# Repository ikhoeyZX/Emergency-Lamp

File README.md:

# Undens Lampu Emergency

This repository contains the source code for build a Emergency lamp based STM8 or ESP8266.

* Note: ESP8266 version are __not recommended__ but you can build it, but beware it sometimes crash and heating up when using step-up ic / module at low battery level (below 3V)

# Reason?

In my country there is much earthquake, well because i'm life in ring of fire area, i did experience big earthquake back in 2017. When earthquake happen, my family still sleeping (it around 12AM) and got blackout, there is no way to find door or find a place to protect our selfes because it's too dark to see. So that's why i make this in case it happen again we still got light to find exit or place to protect out selfes.

Most commercial emergency lamp in here are bad because cheap battery (only last 1 year and only hold 1.5h every running) and didn't have protection charger!!

# What version i should make?

There is 2 build exist (ESP8266 and STM8, arduino series will added later) for 1 layer recommended use v1.2 and for 2 layers smd build use v1.3

each folder contains how to build it. You need Android IDE to program it (in STM8 case, make sure your username in PC doesn't have "space" otherwise SDCPP will fail to build because this bug not yet fixed from SDCC it self).

* Note : For step-up ic/module you can find by self, depend of budget, because MOSFET output only act as "switch" so you need step-up to make sure it can output high voltage to light a leds (5v are common but waste much power, i recommended use 4.3v output to reduce power usage)
* MOSFET should be withstand around ~4A continues with heatsink, so if you using step-up and output set 4.3v it should be around ~4A Max in input side
* In my case only use 1A at MOSFET output and 4400mA battery. it can run without issue around 4H with 20 leds (~30mA/leds) in 12 places at home.

## Finished device:

|                      **Main device**                          |                                      **A Step up ic MT3608**                                   |
| :-----------------------------------------------------------: | :--------------------------------------------------------------------------------------------: |
|                       |                                                         |

|               **Main device when running**                    |                  **A led that used, smd led 3v with 5v input (with 47ohm resistor)**           |
| :-----------------------------------------------------------: | :--------------------------------------------------------------------------------------------: |
|          |  |

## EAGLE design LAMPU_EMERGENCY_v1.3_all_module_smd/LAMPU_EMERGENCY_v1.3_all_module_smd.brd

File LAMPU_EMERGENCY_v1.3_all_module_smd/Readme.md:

To make this follow "Build.png"

for output you need external step-up, you can use MT3608 / QC 3.0 or other step-up, 5v output is recommended for better battery life

for 2A or higher put heatsink in MOSFET!

for speaker, this build use "buzzer type"

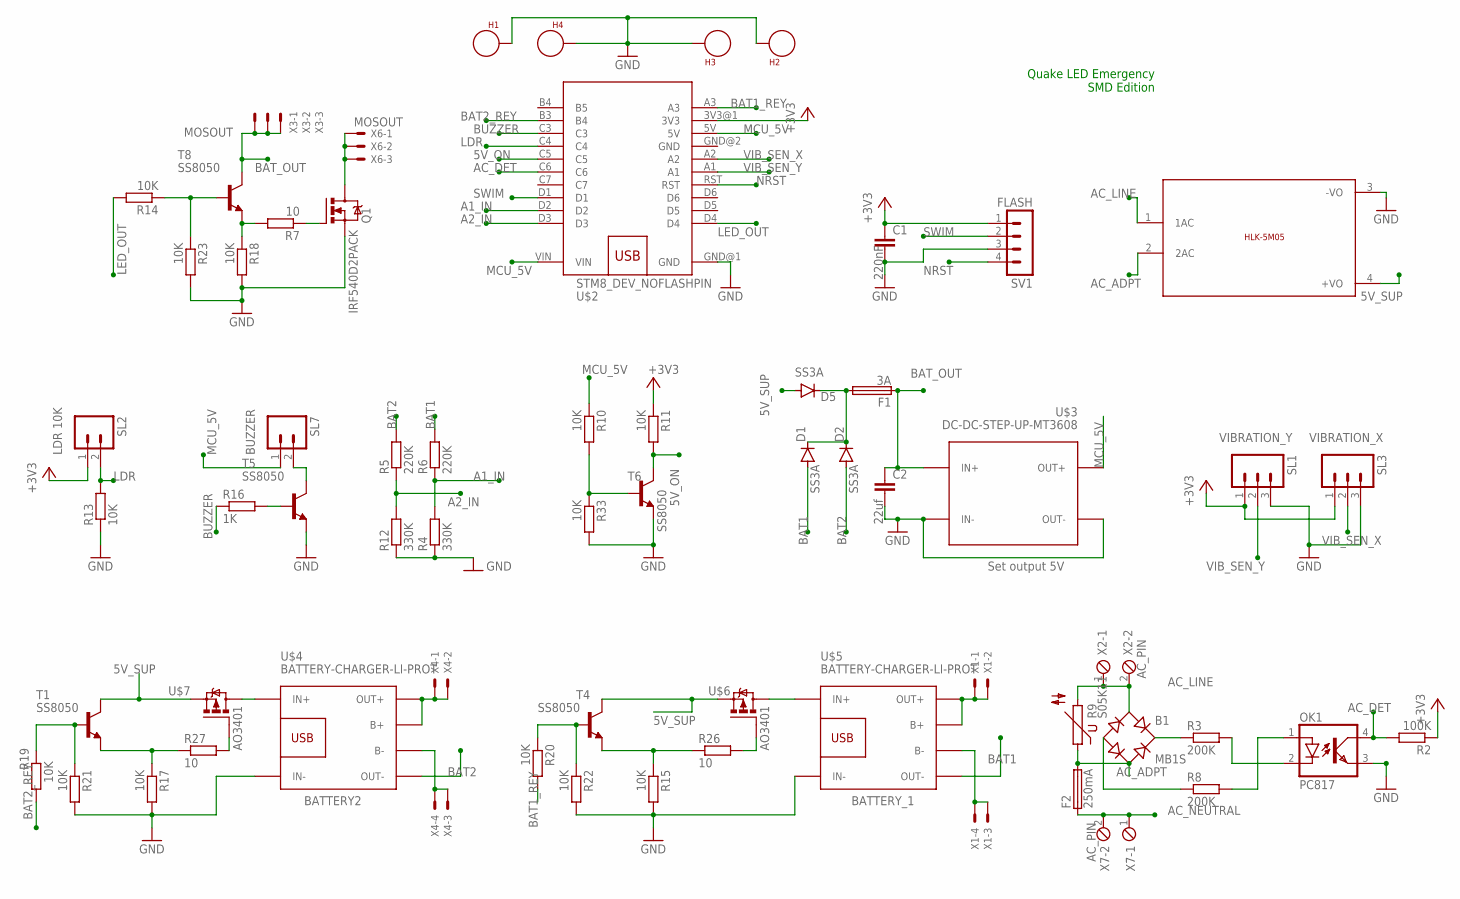
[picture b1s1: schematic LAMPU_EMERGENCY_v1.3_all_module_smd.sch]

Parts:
B1: MB1S; SOIC-4
C1: 220nF; C0805K
C2: 22uf; C0805K
D1, D2, D5: SS3A; SMB
F1: 3A; GSH15
F2: 250mA; TR5
H1, H2, H3, H4: SEW_HOLE; SIMPLE_HOLE
OK1: PC817; DIL04
Q1: IRF540D2PACK; D2PACK
R2: 100K; M1206
R3, R8: 200K; 0922V
R4, R12: 330K; M1206
R5, R6: 220K; M1206
R7, R26, R27: 10; M1206
R9: S05K11
R10, R11, R13, R14, R15, R17, R18, R19, R20, R21, R22, R23, R33: 10K; M1206
R16: 1K; M1206
SL1: VIBRATION_Y; 03P
SL2: LDR 10K; 02P
SL3: VIBRATION_X; 03P
SL7: BUZZER; 02P
SV1: FLASH; MA04-1
T1, T4, T5, T6, T8: SS8050; SOT23
U$1: 5VDC/5W; HLK-5M05
U$2: STM8_DEV_NOFLASHPIN; NO_FLASH_PIN
U$3: DC-DC-STEP-UP-MT3608
U$4, U$5: BATTERY-CHARGER-LI-PROT
U$6, U$7: AO3401; SOT23
X1: BATTERY_1; 22-23-2041
X2, X7: AC_PIN; 2POL254
X3, X6: MOSOUT; 22-23-2031
X4: BATTERY2; 22-23-2041

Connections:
5V_ON: R11.2, T6.3 (C), U$2.C5
5V_SUP: D5.A, T1.3 (C), T4.3 (C), U$1.4 (+VO), U$6.3 (S), U$7.3 (S)
+3V3: C1.1, R2.1, R11.1, SL1.1, SL2.1, SL3.1, SV1.1, U$2.3V3@1 (3V3)
A1_IN: R4.2, R6.1, U$2.D2
A2_IN: R5.1, R12.2, U$2.D3
AC_ADPT: B1.~2 (AC2), F2.2, R9.1, U$1.2 (2AC)
AC_DET: OK1.4 (COL), R2.2, U$2.C6
AC_LINE: B1.~1 (AC1), R9.2, U$1.1 (1AC), X2.1, X2.2
AC_NEUTRAL: F2.1, X7.1, X7.2
BAT1: D1.A, R6.2, U$5.OUT-
BAT1_REY: R20.2, U$2.A3
BAT2: D2.A, R5.2, U$4.OUT-
BAT2_REY: R19.1, U$2.B3 (B4)
BAT_OUT: C2.1, F1.1, T8.3 (C), U$3.IN+, X3.1, X3.2, X3.3
BUZZER: R16.1, U$2.C3
GND: C1.2, C2.2, H1.P$1, H2.P$1, H3.P$1, H4.P$1, OK1.3 (EMIT), Q1.3 (S), R4.1, R12.1, R13.1, R15.2, R17.2, R18.2, R21.2, R22.2, R23.2, R33.2, SL1.3, SL3.3, SV1.3, T5.2 (E), T6.2 (E), U$1.3 (-VO), U$2.GND@1 (GND), U$2.GND@2 (GND), U$3.IN-, U$3.OUT-, U$4.IN-, U$5.IN-
LDR: R13.2, SL2.2, U$2.C4
LED_OUT: R14.2, U$2.D4
MCU_5V: R10.1, SL7.1, U$2.5V, U$2.VIN, U$3.OUT+
unnamed: OK1.2 (C), R3.2
unnamed: R10.2, R33.1, T6.1 (B)
unnamed: B1.+, R3.1
unnamed: B1.-, R8.1
unnamed: OK1.1 (A), R8.2
unnamed: U$4.B+, U$4.OUT+, X4.1, X4.2
unnamed: Q1.1 (G), R7.1
unnamed: R26.2, U$6.1 (G)
unnamed: U$5.IN+, U$6.2 (D)
unnamed: U$4.B-, X4.3, X4.4
unnamed: U$5.B+, U$5.OUT+, X1.1, X1.2
unnamed: R15.1, R26.1, T4.2 (E)
unnamed: SL7.2, T5.3 (C)
unnamed: R27.2, U$7.1 (G)
unnamed: D1.C, D2.C, D5.C, F1.2
unnamed: R16.2, T5.1 (B)
unnamed: U$5.B-, X1.3, X1.4
unnamed: R19.2, R21.1, T1.1 (B)
unnamed: R7.2, R18.1, T8.2 (E)
unnamed: R14.1, R23.1, T8.1 (B)
unnamed: Q1.2 (D), X6.1, X6.2, X6.3
unnamed: R17.1, R27.1, T1.2 (E)
unnamed: R20.1, R22.1, T4.1 (B)
unnamed: U$4.IN+, U$7.2 (D)
NRST: SV1.4, U$2.RST
SWIM: SV1.2, U$2.D1
VIB_SEN_X: SL3.2, U$2.A2
VIB_SEN_Y: SL1.2, U$2.A1

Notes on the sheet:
Quake LED Emergency SMD Edition
Set output 5V

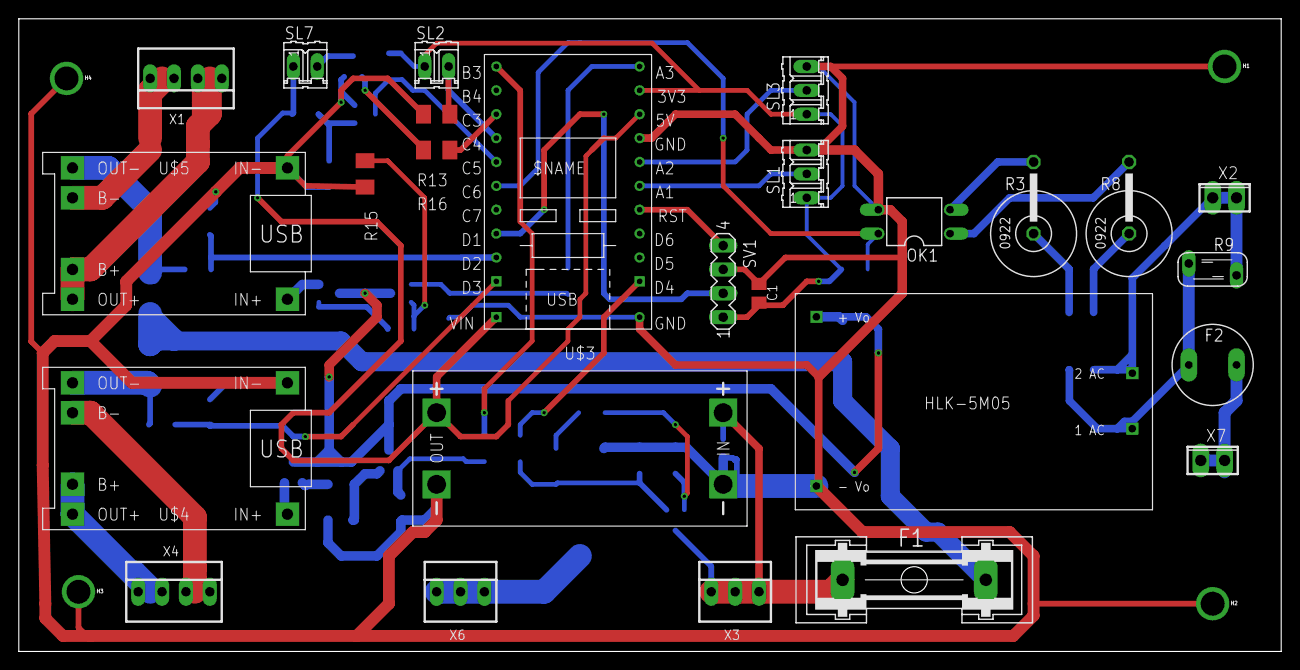
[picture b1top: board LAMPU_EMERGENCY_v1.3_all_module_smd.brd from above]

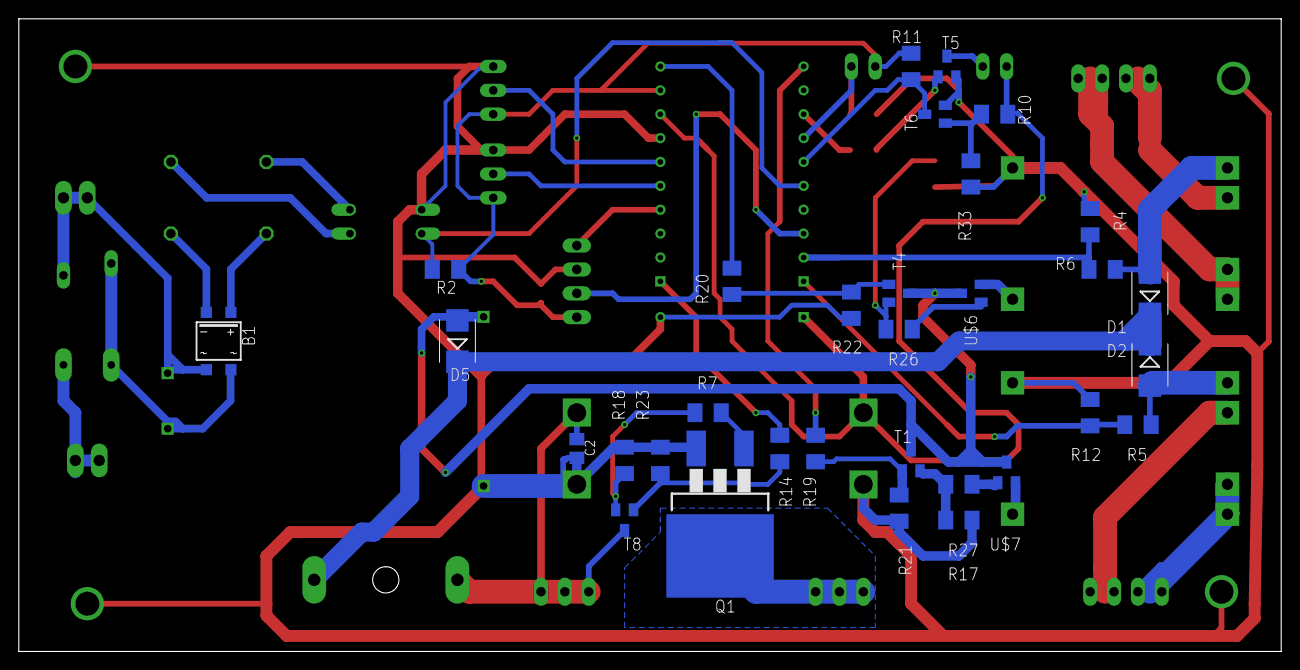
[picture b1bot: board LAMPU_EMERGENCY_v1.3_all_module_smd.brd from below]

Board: 2 copper layers, 134.3 x 67.3 mm, 62 parts (32 on the bottom side), 47 nets.

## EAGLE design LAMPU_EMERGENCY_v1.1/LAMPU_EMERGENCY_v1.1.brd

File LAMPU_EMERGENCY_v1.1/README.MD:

this module using external battery charger

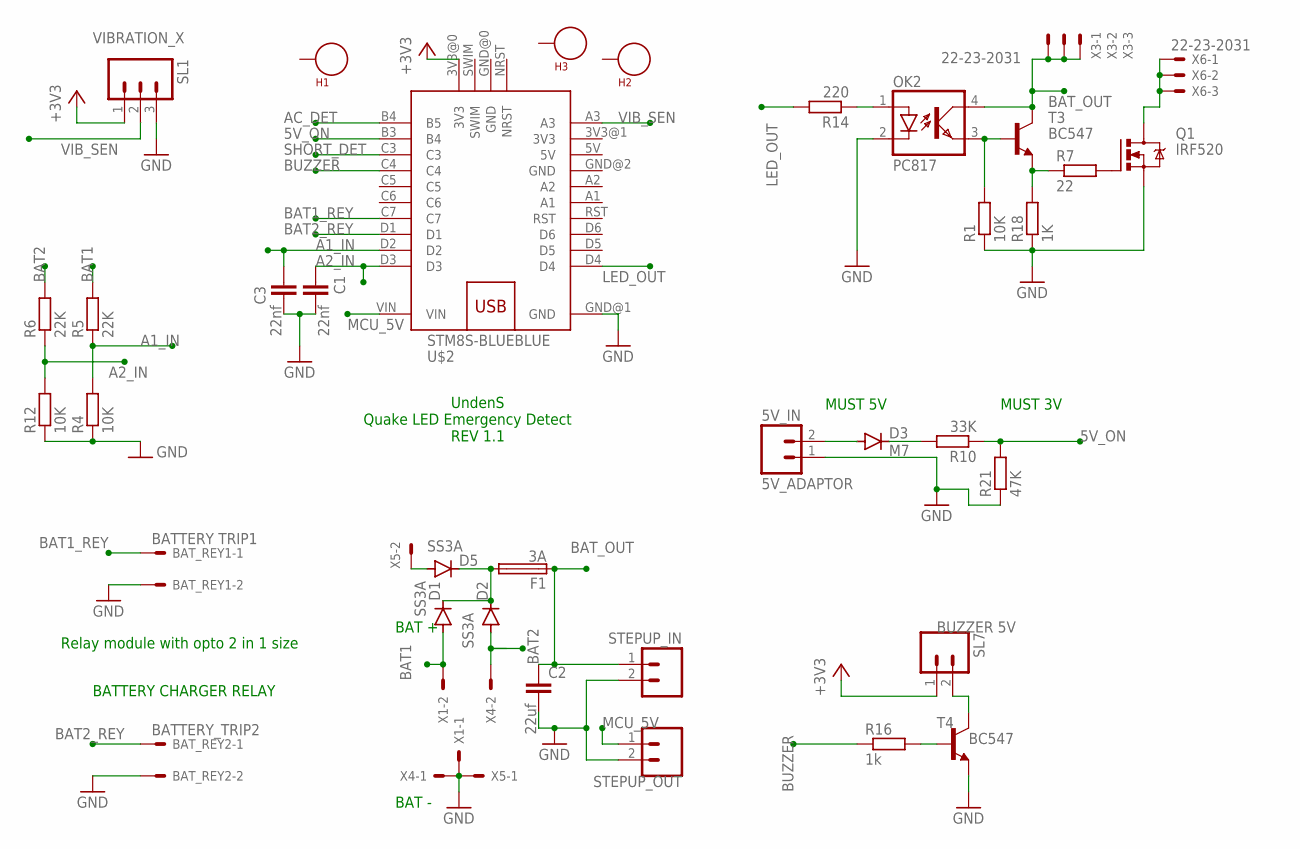
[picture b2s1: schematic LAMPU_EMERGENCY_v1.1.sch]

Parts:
5V_IN: 5V_ADAPTOR; 02P
BAT_REY1: BATTERY TRIP1; 22-23-2021
BAT_REY2: BATTERY_TRIP2; 22-23-2021
C1, C3: 22nf; C0805K
C2: 22uf; C0805K
D1, D2, D5: SS3A; SMB
D3: M7; SMB
F1: 3A; GSH15
H1, H2, H3: SEW_HOLE; SIMPLE_HOLE
OK2: PC817; DIL04
Q1: IRF520; TO220BV
R1, R4, R12: 10K; 0207/7
R5, R6: 22K; 0207/7
R7: 22; 0207/7
R10: 33K; 0207/7
R14: 220; 0207/7
R16: 1k; 0207/7
R18: 1K; 0207/7
R21: 47K; 0207/7
SL1: VIBRATION_X; 03P
SL7: BUZZER 5V; 02P
STEP_IN: STEPUP_IN; 02P
STEP_MCU: STEPUP_OUT; 02P
T3, T4: BC547; TO92
U$2: STM8S-BLUEBLUE; WEMOS-D1-MINI
X1, X4, X5: 22-23-2021
X3, X6: 22-23-2031

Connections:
3V3: U$2.3V3@1 (3V3)
5V: U$2.5V
5V_ON: R10.1, R21.2, U$2.B3 (B4)
+3V3: SL1.1, SL7.1, U$2.3V3@0 (3V3)
A1_IN: C3.1, R4.2, R5.1, U$2.D2
A2_IN: C1.1, R6.1, R12.2, U$2.D3
AC_DET: U$2.B4 (B5)
BAT1: D1.A, R5.2, X1.2
BAT1_REY: BAT_REY1.1, U$2.C7
BAT2: D2.A, R6.2, X4.2
BAT2_REY: BAT_REY2.1, U$2.D1
BAT_OUT: C2.1, F1.1, OK2.4 (COL), STEP_IN.1, T3.3 (C), X3.1, X3.2, X3.3
BUZZER: R16.1, U$2.C4
GND: 5V_IN.1, BAT_REY1.2, BAT_REY2.2, C1.2, C2.2, C3.2, OK2.2 (C), Q1.S, R1.1, R4.1, R12.1, R18.1, R21.1, SL1.3, STEP_IN.2, STEP_MCU.2, T4.1 (E), U$2.GND@1 (GND), U$2.GND@2 (GND), X1.1, X4.1, X5.1
LED_OUT: R14.2, U$2.D4
MCU_5V: STEP_MCU.1, U$2.VIN
unnamed: OK2.3 (EMIT), R1.2, T3.2 (B)
unnamed: 5V_IN.2, D3.A
unnamed: SL7.2, T4.3 (C)
unnamed: D1.C, D2.C, D5.C, F1.2
unnamed: R16.2, T4.2 (B)
unnamed: R7.1, R18.2, T3.1 (E)
unnamed: Q1.G, R7.2
unnamed: OK2.1 (A), R14.1
unnamed: Q1.D, X6.1, X6.2, X6.3
unnamed: D3.C, R10.2
unnamed: D5.A, X5.2
SHORT_DET: U$2.C3
VIB_SEN: SL1.2, U$2.A3

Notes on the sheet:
BAT +
BAT -
BATTERY CHARGER RELAY
Relay module with opto 2 in 1 size
MUST 3V
MUST 5V
UndenS Quake LED Emergency Detect REV 1.1

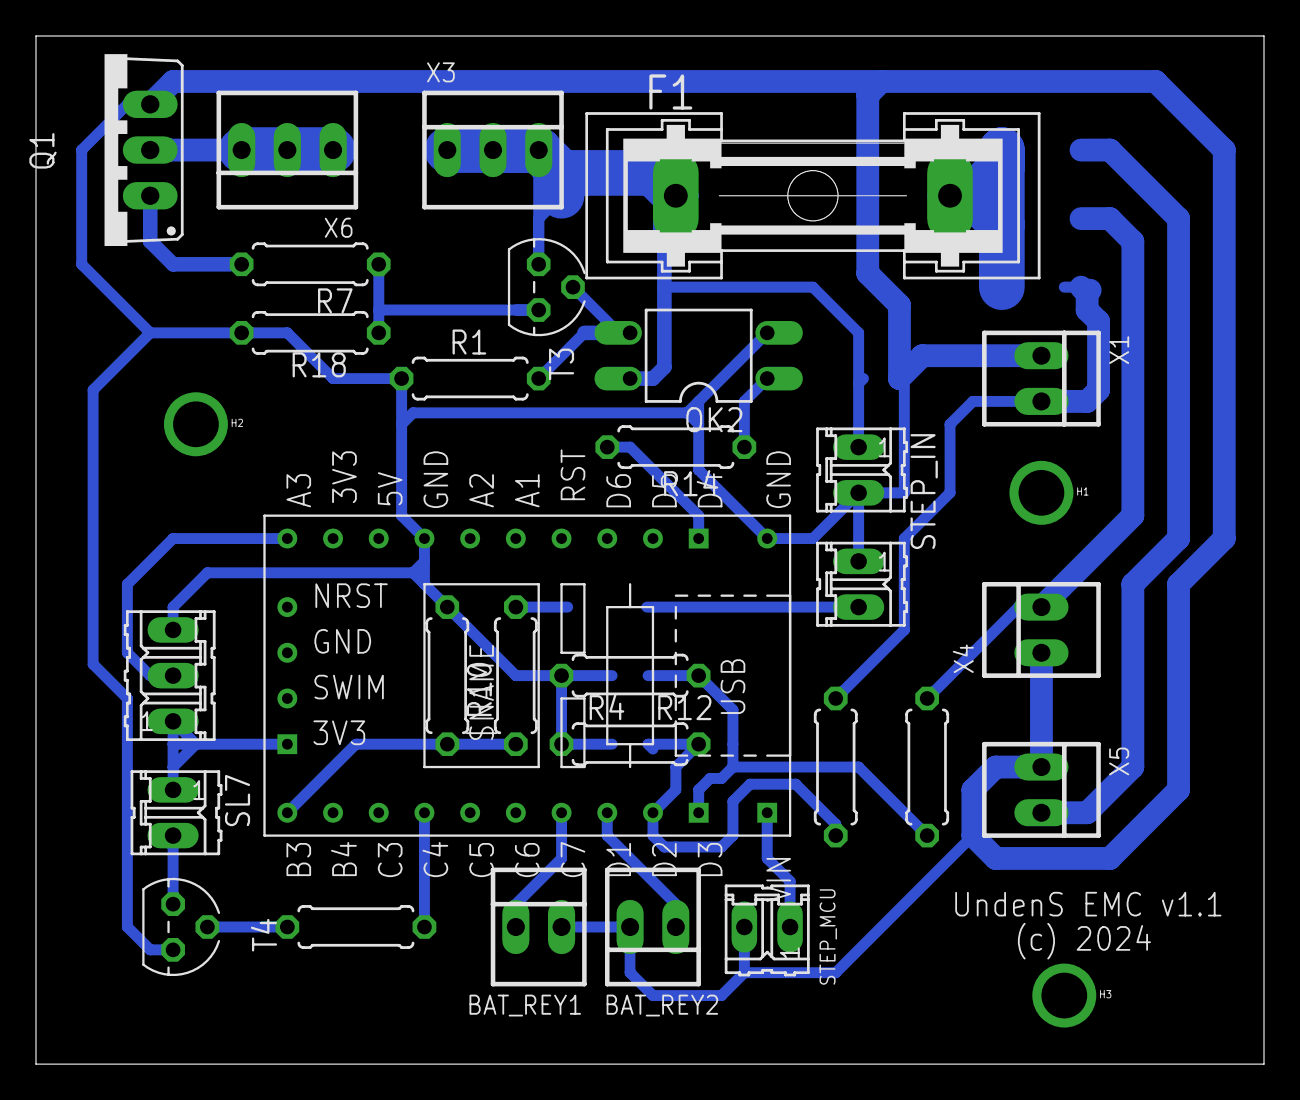
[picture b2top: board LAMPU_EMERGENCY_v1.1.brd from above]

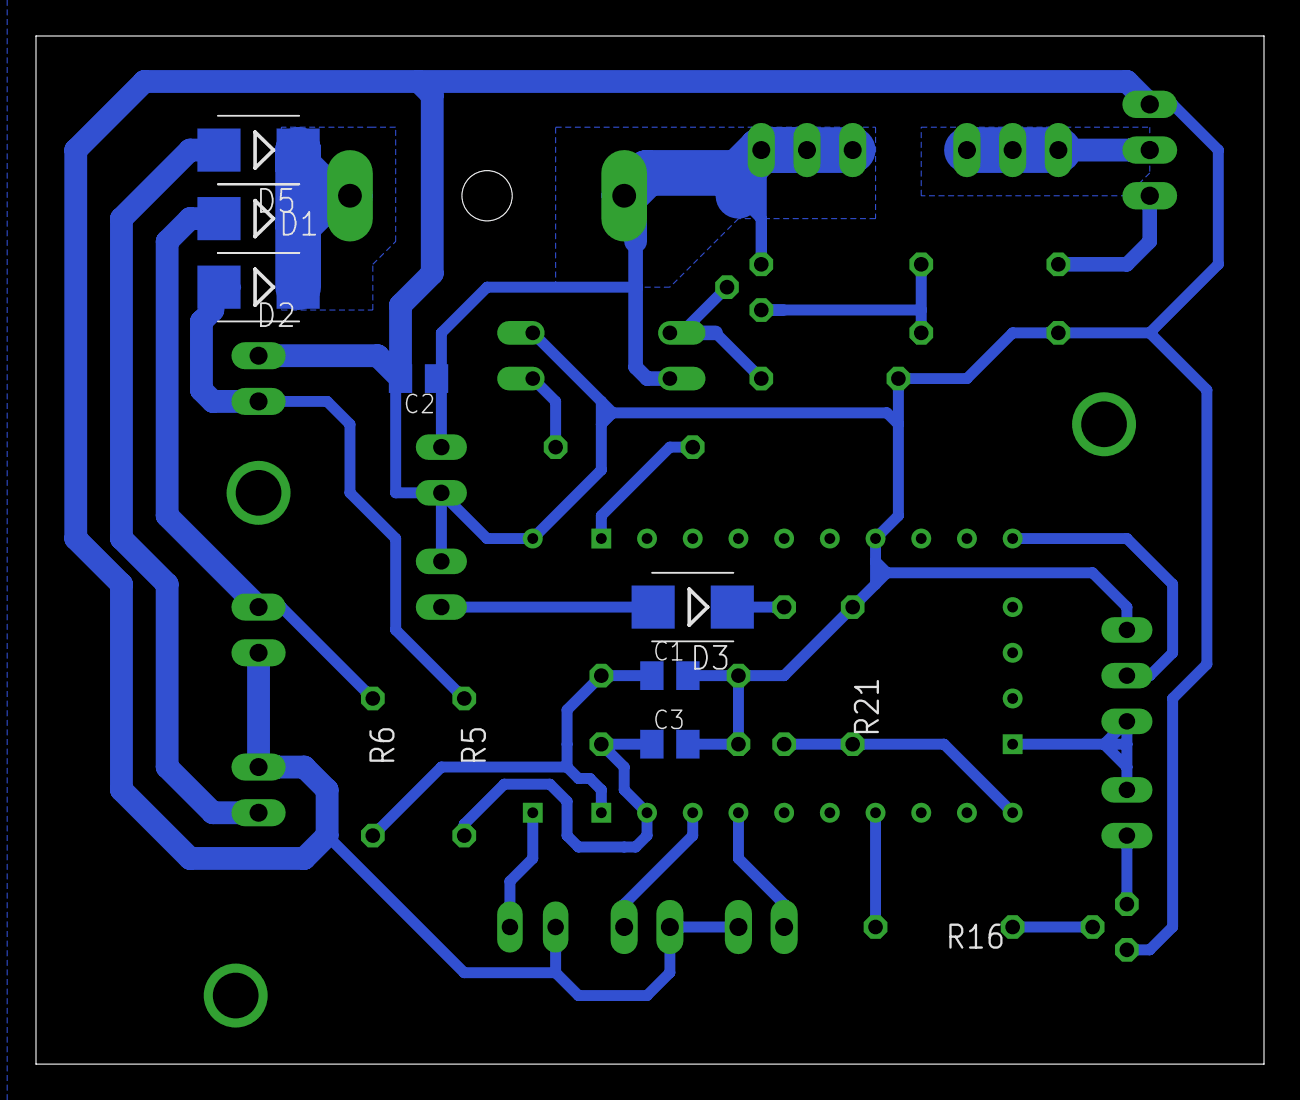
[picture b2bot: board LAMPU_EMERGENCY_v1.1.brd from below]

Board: 2 copper layers, 68.2 x 57.1 mm, 39 parts (7 on the bottom side), 25 nets.

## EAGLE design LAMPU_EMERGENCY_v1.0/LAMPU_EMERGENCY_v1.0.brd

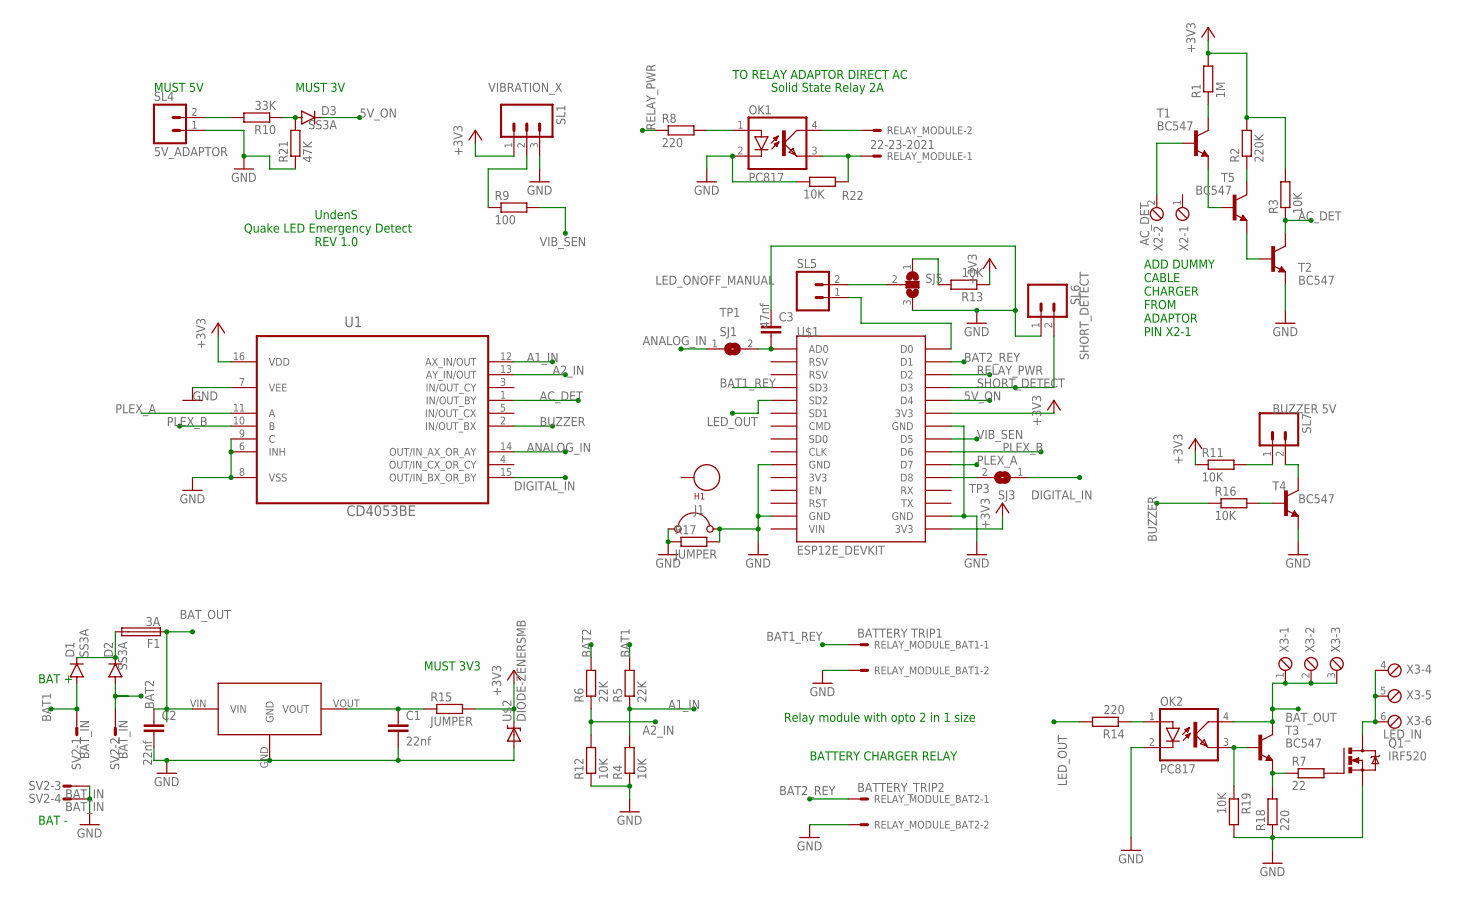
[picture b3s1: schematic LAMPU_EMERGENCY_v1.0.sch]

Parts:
C1, C2: 22nf; C0805K
C3: 47nf; C0805K
D1, D2, D3: SS3A; SMB
F1: 3A; GSH15
H1: SEW_HOLE; SIMPLE_HOLE
J1: JUMPER; 05
OK1, OK2: PC817; DIL04
Q1: IRF520; TO220BV
R1: 1M; 0207/7
R2: 220K; 0207/7
R3, R4, R11, R12, R13, R16, R19, R22: 10K; 0207/7
R5, R6: 22K; 0207/7
R7: 22; 0207/7
R8, R14, R18: 220; 0207/7
R9: 100; 0207/7
R10: 33K; 0207/7
R15: JUMPER; 0207/15
R17: JUMPER; 0207/7
R21: 47K; 0207/7
RELAY_MODULE: 22-23-2021
RELAY_MODULE_BAT1: BATTERY TRIP1; 22-23-2021
RELAY_MODULE_BAT2: BATTERY_TRIP2; 22-23-2021
SJ1: TP1; SJW
SJ3: TP3; SJW
SJ5: SJ2WW; SJ_2W
SL1: VIBRATION_X; 03P
SL4: 5V_ADAPTOR; 02P
SL5: LED_ONOFF_MANUAL; 02P
SL6: SHORT_DETECT; 02P
SL7: BUZZER 5V; 02P
SV2: BAT_IN; S04P
T1, T2, T3, T4, T5: BC547; TO92
U1: CD4053BE; DIP254P762X508-16
U$1: ESP12E_DEVKIT
U$2: DIODE-ZENERSMB; SMB-DIODE
U$3: HT7333; SOT89
X2: AC_DET; 2POL254
X3: LED_IN; 6POL254

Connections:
5V_ON: D3.C, U$1.D4
+3V3: R1.2, R2.2, R3.2, R11.1, R13.1, R15.2, SL1.1, U1.16 (VDD), U$1.3V3@1 (3V3), U$1.3V3@2 (3V3), U$2.C
A1_IN: R4.2, R5.1, U1.12 (AX_IN/OUT)
A2_IN: R6.1, R12.2, U1.13 (AY_IN/OUT)
AC_DET: R3.1, T2.3 (C), U1.1 (IN/OUT_BY)
ANALOG_IN: SJ1.1, U1.14 (OUT/IN_AX_OR_AY)
BAT1: D1.A, R5.2, SV2.1
BAT1_REY: RELAY_MODULE_BAT1.1, U$1.SD3
BAT2: D2.A, R6.2, SV2.2
BAT2_REY: RELAY_MODULE_BAT2.1, U$1.D1
BAT_OUT: C2.1, F1.1, OK2.4 (COL), T3.3 (C), U$3.VIN, X3.1, X3.2, X3.3
BUZZER: R16.1, U1.2 (IN/OUT_BX)
DIGITAL_IN: SJ3.1, U1.15 (OUT/IN_BX_OR_BY)
GND: C1.2, C2.2, C3.1, J1.1 (+), J1.2 (-), OK1.2 (C), OK2.2 (C), Q1.S, R4.1, R12.1, R17.1, R17.2, R18.1, R19.2, R21.1, R22.1, RELAY_MODULE_BAT1.2, RELAY_MODULE_BAT2.2, SJ5.3, SL1.3, SL4.1, SL6.1, SV2.3, SV2.4, T2.1 (E), T4.1 (E), U1.6 (INH), U1.7 (VEE), U1.8 (VSS), U1.9 (C), U$1.GND@0 (GND), U$1.GND@1 (GND), U$1.GND@2 (GND), U$1.GND@3 (GND), U$2.A, U$3.GND
LED_OUT: R14.2, U$1.SD2
unnamed: SJ3.2, U$1.D8
unnamed: R1.1, T1.3 (C)
unnamed: T1.1 (E), T5.2 (B)
unnamed: R2.1, T5.3 (C)
unnamed: T2.2 (B), T5.1 (E)
unnamed: T1.2 (B), X2.2
unnamed: R13.2, SJ5.1
unnamed: OK1.1 (A), R8.2
unnamed: OK1.4 (COL), RELAY_MODULE.2
unnamed: OK1.3 (EMIT), R22.2, RELAY_MODULE.1
unnamed: C3.2, SJ1.2, U$1.AD0
unnamed: R11.2, SL7.1
unnamed: R9.1, SL1.2
unnamed: SL7.2, T4.3 (C)
unnamed: D3.A, R10.1, R21.2
unnamed: D1.C, D2.C, F1.2
unnamed: R16.2, T4.2 (B)
unnamed: SL5.1, U$1.D0
unnamed: OK2.3 (EMIT), R19.1, T3.2 (B)
unnamed: R7.1, R18.2, T3.1 (E)
unnamed: Q1.G, R7.2
unnamed: OK2.1 (A), R14.1
unnamed: Q1.D, X3.4, X3.5, X3.6
unnamed: R10.2, SL4.2
unnamed: C1.1, R15.1, U$3.VOUT
unnamed: SJ5.2, SL5.2
PLEX_A: U1.11 (A), U$1.D7
PLEX_B: U1.10 (B), U$1.D6
RELAY_PWR: R8.1, U$1.D2
SHORT_DETECT: SL6.2, U$1.D3
VIB_SEN: R9.2, U$1.D5

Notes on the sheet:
MUST 3V3
ADD DUMMY CABLE CHARGER FROM ADAPTOR PIN X2-1
BAT +
BAT -
TO RELAY ADAPTOR DIRECT AC
BATTERY CHARGER RELAY
Solid State Relay 2A
Relay module with opto 2 in 1 size
MUST 3V
MUST 5V
UndenS Quake LED Emergency Detect REV 1.0

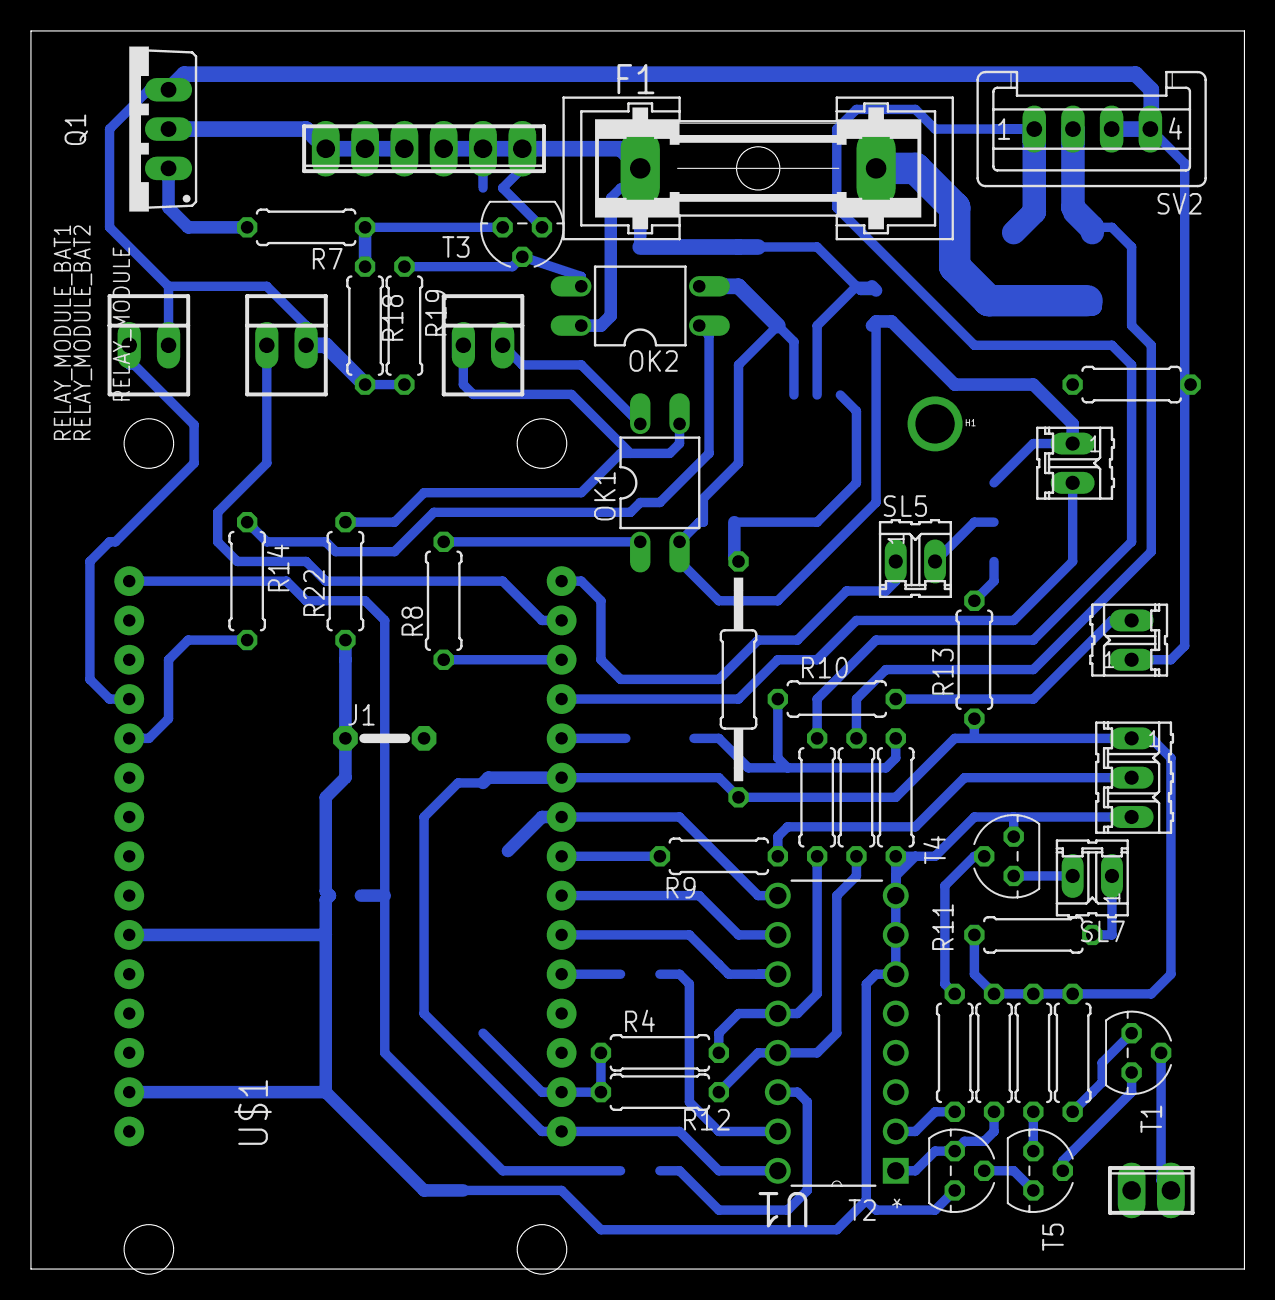
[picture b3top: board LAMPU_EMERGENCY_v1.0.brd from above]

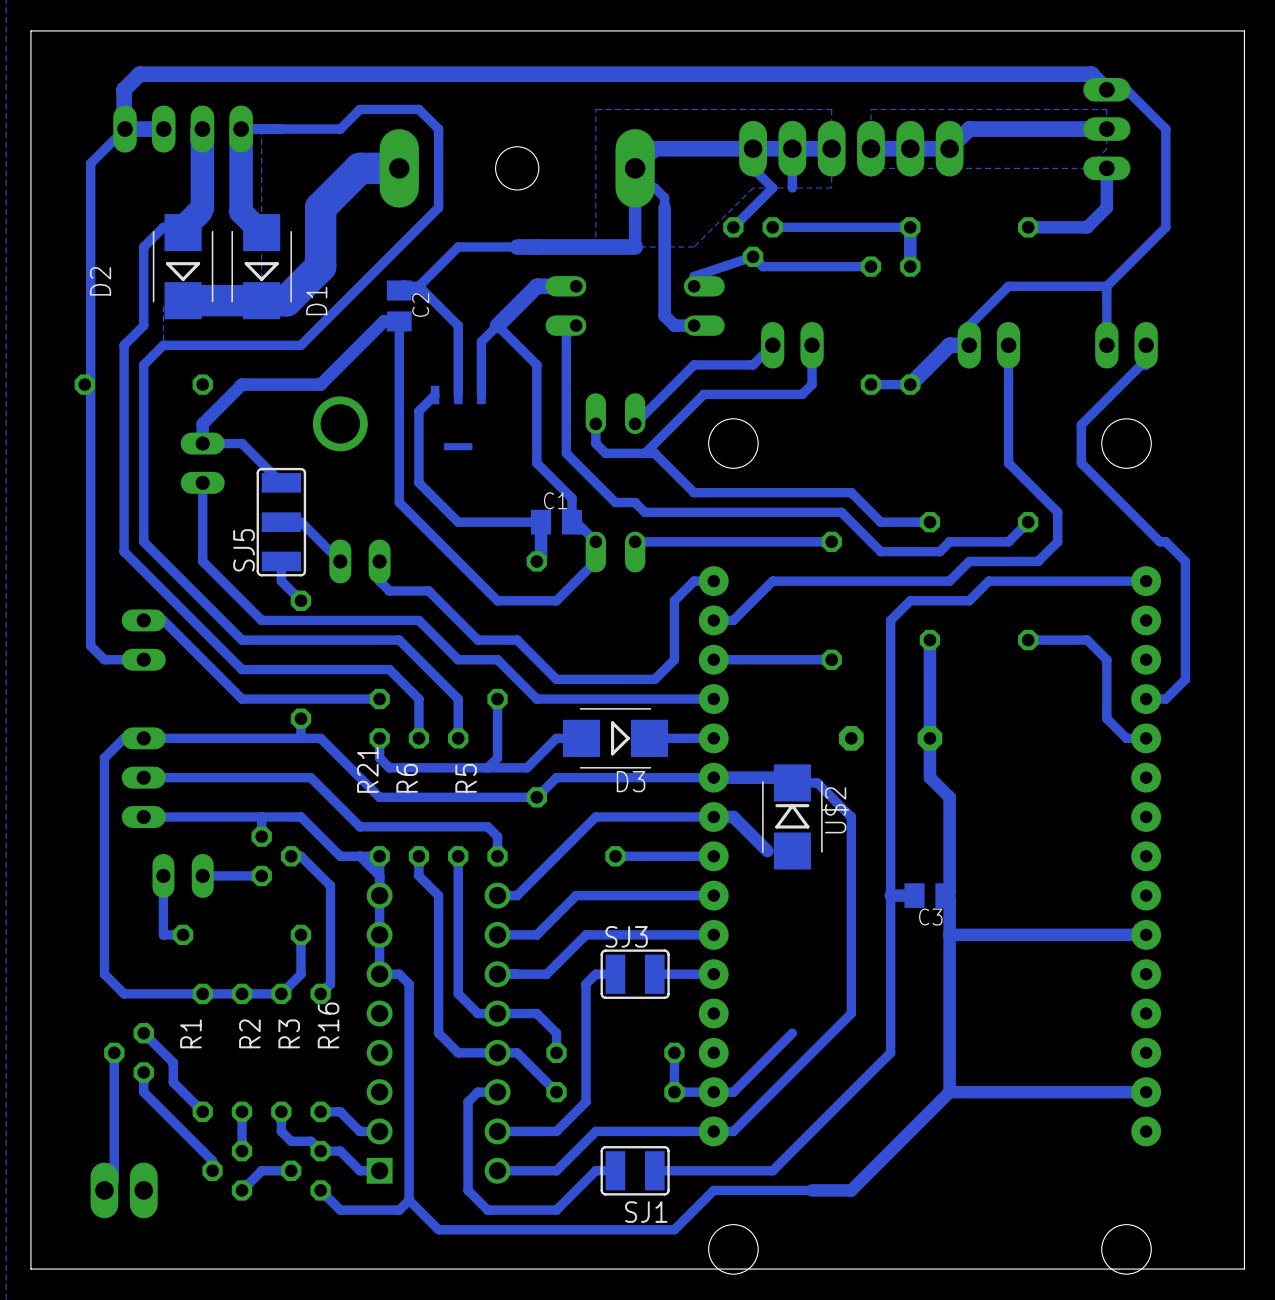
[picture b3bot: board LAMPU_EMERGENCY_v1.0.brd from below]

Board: 2 copper layers, 78.4 x 80.0 mm, 56 parts (11 on the bottom side), 46 nets.

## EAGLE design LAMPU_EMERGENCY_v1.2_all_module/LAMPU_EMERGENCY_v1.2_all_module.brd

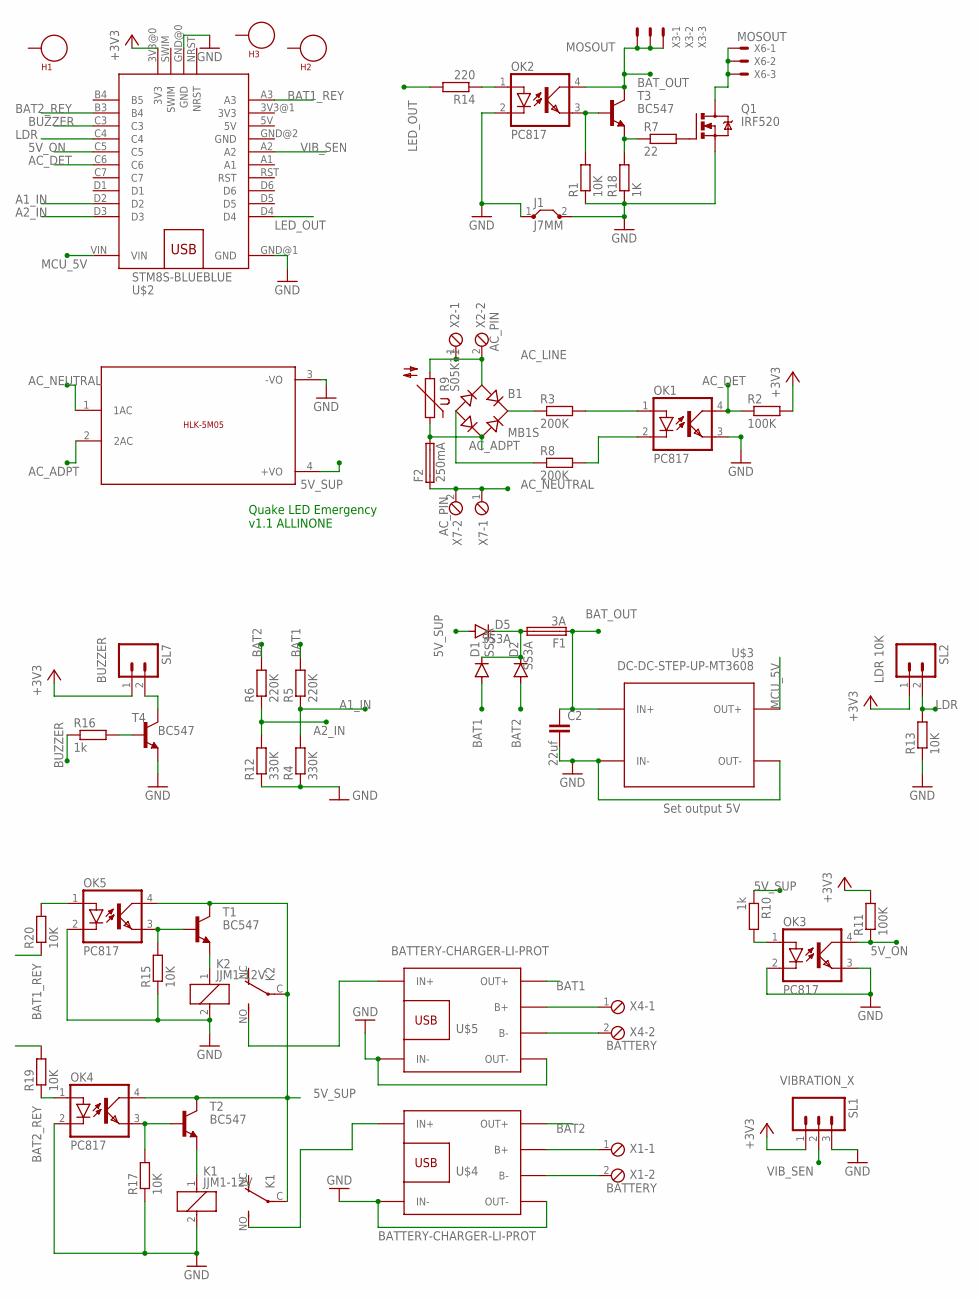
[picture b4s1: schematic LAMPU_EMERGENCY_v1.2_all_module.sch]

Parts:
B1: MB1S; SOIC-4
C2: 22uf; C0805K
D1, D2, D5: SS3A; SMB
F1: 3A; GSH15
F2: 250mA; TR5
H1, H2, H3: SEW_HOLE; SIMPLE_HOLE
J1: J7MM; 07
K1, K2: JJM1-12V; JJM1C
OK1, OK2, OK3, OK4, OK5: PC817; DIL04
Q1: IRF520; TO220BV
R1, R13, R15, R17, R19, R20: 10K; 0207/7
R2, R11: 100K; 0207/7
R3, R8: 200K; 0922V
R4, R12: 330K; 0207/7
R5, R6: 220K; 0207/7
R7: 22; 0207/7
R9: S05K11
R10, R16: 1k; 0207/7
R14: 220; 0207/7
R18: 1K; 0207/7
SL1: VIBRATION_X; 03P
SL2: LDR 10K; 02P
SL7: BUZZER; 02P
T1, T2, T3, T4: BC547; TO92
U$1: 5VDC/5W; HLK-5M05
U$2: STM8S-BLUEBLUE; WEMOS-D1-MINI
U$3: DC-DC-STEP-UP-MT3608
U$4, U$5: BATTERY-CHARGER-LI-PROT
X1, X4: BATTERY; 2POL254
X2, X7: AC_PIN; 2POL254
X3, X6: MOSOUT; 22-23-2031

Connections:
3V3: U$2.3V3@1 (3V3)
5V: U$2.5V
5V_ON: OK3.4 (COL), R11.1, U$2.C5
5V_SUP: D5.A, K1.C, K2.C, OK4.4 (COL), OK5.4 (COL), R10.1, T1.3 (C), T2.3 (C), U$1.4 (+VO)
+3V3: R2.2, R11.2, SL1.1, SL2.1, SL7.1, U$2.3V3@0 (3V3)
A1_IN: R4.2, R5.1, U$2.D2
A2_IN: R6.1, R12.2, U$2.D3
AC_ADPT: B1.~2 (AC2), F2.2, R9.1, U$1.2 (2AC)
AC_DET: OK1.4 (COL), R2.1, U$2.C6
AC_LINE: B1.~1 (AC1), R9.2, X2.1, X2.2
AC_NEUTRAL: F2.1, U$1.1 (1AC), X7.1, X7.2
BAT1: D1.A, R5.2, U$5.OUT+
BAT1_REY: R20.1, U$2.A3
BAT2: D2.A, R6.2, U$4.OUT+
BAT2_REY: R19.2, U$2.B3 (B4)
BAT_OUT: C2.1, F1.1, OK2.4 (COL), T3.3 (C), U$3.IN+, X3.1, X3.2, X3.3
BUZZER: R16.1, U$2.C3
GND: C2.2, J1.1, J1.2, K1.2, K2.2, OK1.3 (EMIT), OK2.2 (C), OK3.2 (C), OK3.3 (EMIT), OK4.2 (C), OK5.2 (C), Q1.S, R1.1, R4.1, R12.1, R13.1, R15.1, R17.1, R18.1, SL1.3, T4.1 (E), U$1.3 (-VO), U$2.GND@0 (GND), U$2.GND@1 (GND), U$2.GND@2 (GND), U$3.IN-, U$3.OUT-, U$4.IN-, U$4.OUT-, U$5.IN-, U$5.OUT-
LDR: R13.2, SL2.2, U$2.C4
LED_OUT: R14.2, U$2.D4
MCU_5V: U$2.VIN, U$3.OUT+
unnamed: OK2.3 (EMIT), R1.2, T3.2 (B)
unnamed: OK3.1 (A), R10.2
unnamed: B1.+, R3.1
unnamed: B1.-, R8.1
unnamed: OK1.2 (C), R8.2
unnamed: K1.NO (S), U$4.IN+
unnamed: OK1.1 (A), R3.2
unnamed: K2.NO (S), U$5.IN+
unnamed: U$4.B-, X1.2
unnamed: U$4.B+, X1.1
unnamed: U$5.B-, X4.2
unnamed: U$5.B+, X4.1
unnamed: OK5.3 (EMIT), R15.2, T1.2 (B)
unnamed: SL7.2, T4.3 (C)
unnamed: K2.1, T1.1 (E)
unnamed: D1.C, D2.C, D5.C, F1.2
unnamed: R16.2, T4.2 (B)
unnamed: R7.1, R18.2, T3.1 (E)
unnamed: Q1.G, R7.2
unnamed: OK2.1 (A), R14.1
unnamed: Q1.D, X6.1, X6.2, X6.3
unnamed: OK4.3 (EMIT), R17.2, T2.2 (B)
unnamed: K1.1, T2.1 (E)
unnamed: OK5.1 (A), R20.2
unnamed: OK4.1 (A), R19.1
VIB_SEN: SL1.2, U$2.A2

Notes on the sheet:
Quake LED Emergency v1.1 ALLINONE
Set output 5V

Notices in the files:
LAMPU_EMERGENCY_v1.1/LAMPU_EMERGENCY_v1.1.brd:
(c) 2024
parts and their libraries:
SparkFun-DiscreteSemi: Licensing: CC v3.0 Share-Alike You are welcome to use this library for commercial purposes.
diy-modules: Released under the Creative Commons Attribution 4.0 International License: http://creativecommons.org/licenses/by/4.0
